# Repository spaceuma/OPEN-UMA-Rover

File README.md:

# UMA Open Source Rover ROS2
Open hardware and software rover developed by Malaga University

*Authors:* C.J. Pérez del Pulgar, Ricardo Sánchez Ibáñez, Patricio López Lupiañez, Francisco de Asís Delgado Rivero, Laura Marta Mantoani and Danil Rivero Pavlenko

*Contact info:* carlosperez@uma.es

*Affiliation:* University of Malaga, [Space Robotics Lab](https://www.uma.es/robotics-and-mechatronics/info/107542/robotica-espacial/)

## Overview
The OpenUmaRov is an open source mobile robotic platform that allows anyone to build it with a maximum cost of 700€, taking into account that the Reach M+ GPS can be replaced with whatever GPS that works with NMEA sentences: just connecting it to the Raspberry Pi through USB port, thanks to the ROS node the GPS can publish NMEA sentences in different topics. This means that, replacing the Reach M+ with a cheaper one, the rover can be built with a maximum cost of 500 €. 

The platform is based on commercial components that can be acquired by Internet. This project involves students and researchers to improve the development of the platform. Moreover, it can be used for teaching and research activities that involves mechanical, engineering, software, electronics and robotics.

## ROS2 

An adaptation of the original code to ROS2 Humble has been developed. This enables the use of the Rover with the Middleware ROS2. 

### Guide

First you need to setup your package and your workspace. Use the package in this repository inside the workspace.

Then make sure to source the package and build the workspace.
```
 source install/setup.bash
 colcon build
```

### Troubleshooting

Issues might appear while setting up your workspace.

- setuptools 58.2 for colcon build sterr output error due to deprecated version.

https://answers.ros.org/question/396439/setuptoolsdeprecationwarning-setuppy-install-is-deprecated-use-build-and-pip-and-other-standards-based-tools/

```
pip install setuptools==58.2.0
```

Install serial
Guide: https://create.arduino.cc/projecthub/ansh2919/serial-communication-between-python-and-arduino-e7cce0

```
pip install pyserial
```

Info. about the Twist format for the msg variable which holds the data received from the topic.

http://docs.ros.org/en/noetic/api/geometry_msgs/html/msg/Twist.html

### Running the node

To run the node once sourced and built.

```
ros2 run rov_node_pkg ROS2UMARov
```

## Rover URDF

In order to test the Rover in a simulated environment, a URDF file of the OpenUMARov has been developed.

## Rover SDF

To implement Rover simulations on Gazebo, it is necessary to develop the SDF Model of it. 

This model uses the following plugins.

- GPS Plugin to simulate such in the simulation environment.
- IMU to simulate the orientation of the Rover.
- Differential drive Model to implement the movement of the Rover 
- Joint State Publisher to know wheels state.

An alternative for NAV2 has been implemented as en extended model.

## Joystick Control

A good way to easily control the Rover is by using the Teleoperation Joystick Control.

By default, it uses the ```ps3_config.yaml``` file.

To test this package a F-710 Game Pad with a USB with Bluetooth connection was used, even though the ```.config``` file is for the PS3 Joystick. If you wish to use a Bluetooh joystick control, you have to edit the directory of the connection to rather the Bluetooth direction, using a USB connection is recommended nonetheless.

To use it with the PC the following changes should be done:

- Add permissions to read/write Serial: 

```
sudo adduser $USER $(stat --format="%G" /dev/ttyACM0)
```

- Build the package with the following command:

```
colcon build --allow-overriding teleop_twist_joy
```

PS3 is default, to run for another config (e.g. xbox) use this:

```
ros2 launch teleop_twist_joy teleop-launch.py
```

Note: this launch file also launches the joy node so do not run it separately.

Only if required:

- Uninstall the default joystick teleop. from ROS2 Lib. Head to opt/ros/lib and remove the file teleop_twist_joy. 
- The last step is due to ROS2 using the config. of the default driver and its parameters instead of your package.
- Launch the driver as normally.

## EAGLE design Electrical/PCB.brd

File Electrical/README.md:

# OPEN-UMA-Rover/Electrical
In this folder there are the files for the PCB board in Eagle, version 7.6.0.

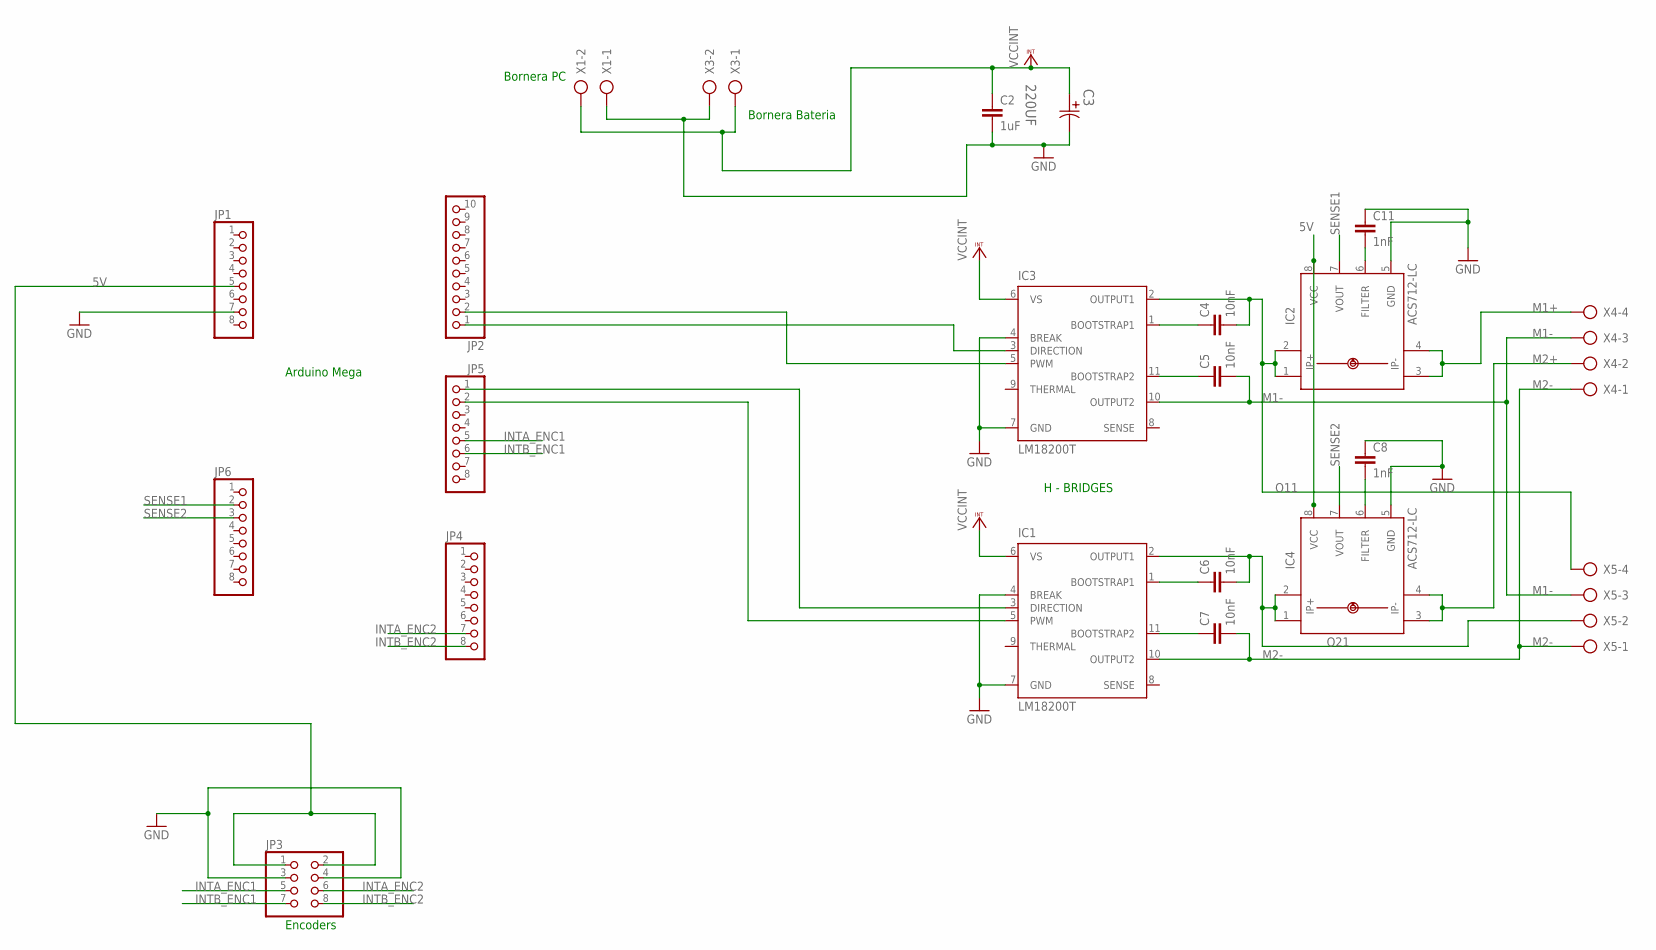
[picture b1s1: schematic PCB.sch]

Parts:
C2: 1uF; C050-030X075
C3: 220UF; CAPPR500-1000X3200
C4, C5, C6, C7: 10nF; C050-030X075
C8, C11: 1nF; C050-030X075
IC1, IC3: LM18200T; TO-220-11
IC2, IC4: ACS712-LC; SOIC8
JP1, JP4, JP5, JP6: PINHD-1X8; 1X08
JP2: PINHD-1X10; 1X10
JP3: PINHD-2X4; 2X04
X1, X3: AK500/2
X4, X5: AK500/4-H

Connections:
5V: IC2.8 (VCC), IC4.8 (VCC), JP1.5, JP3.1, JP3.2
GND: C2.2, C3.2, C8.1, C11.1, IC1.4 (BREAK), IC1.7 (GND), IC2.5 (GND), IC3.4 (BREAK), IC3.7 (GND), IC4.5 (GND), JP1.7, JP3.3, JP3.4, X1.1, X3.2
INTA_ENC1: JP3.5, JP5.5
INTA_ENC2: JP3.6, JP4.7
INTB_ENC1: JP3.7, JP5.6
INTB_ENC2: JP3.8, JP4.8
M1+: IC2.3 (IP-), IC2.4 (IP-1), X4.4
M1-: C5.2, IC3.10 (OUTPUT2), X4.3, X5.3
M2+: IC4.3 (IP-), IC4.4 (IP-1), X4.2
M2-: C7.2, IC1.10 (OUTPUT2), X4.1, X5.1
unnamed: IC3.3 (DIRECTION), JP2.1
unnamed: IC3.5 (PWM), JP2.2
unnamed: IC1.3 (DIRECTION), JP5.1
unnamed: C4.1, IC3.1 (BOOTSTRAP1)
unnamed: IC1.5 (PWM), JP5.2
unnamed: C8.2, IC4.6 (FILTER)
unnamed: C11.2, IC2.6 (FILTER)
unnamed: C5.1, IC3.11 (BOOTSTRAP2)
unnamed: C6.1, IC1.1 (BOOTSTRAP1)
unnamed: C7.1, IC1.11 (BOOTSTRAP2)
O11: C4.2, IC2.1 (IP+), IC2.2 (IP+1), IC3.2 (OUTPUT1), X5.4
O21: C6.2, IC1.2 (OUTPUT1), IC4.1 (IP+), IC4.2 (IP+1), X5.2
SENSE1: IC2.7 (VOUT), JP6.2
SENSE2: IC4.7 (VOUT), JP6.3
VCCINT: C2.1, C3.1, IC1.6 (VS), IC3.6 (VS), X1.2, X3.1

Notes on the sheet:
Encoders
Arduino Mega
H - BRIDGES
Bornera Bateria
Bornera PC

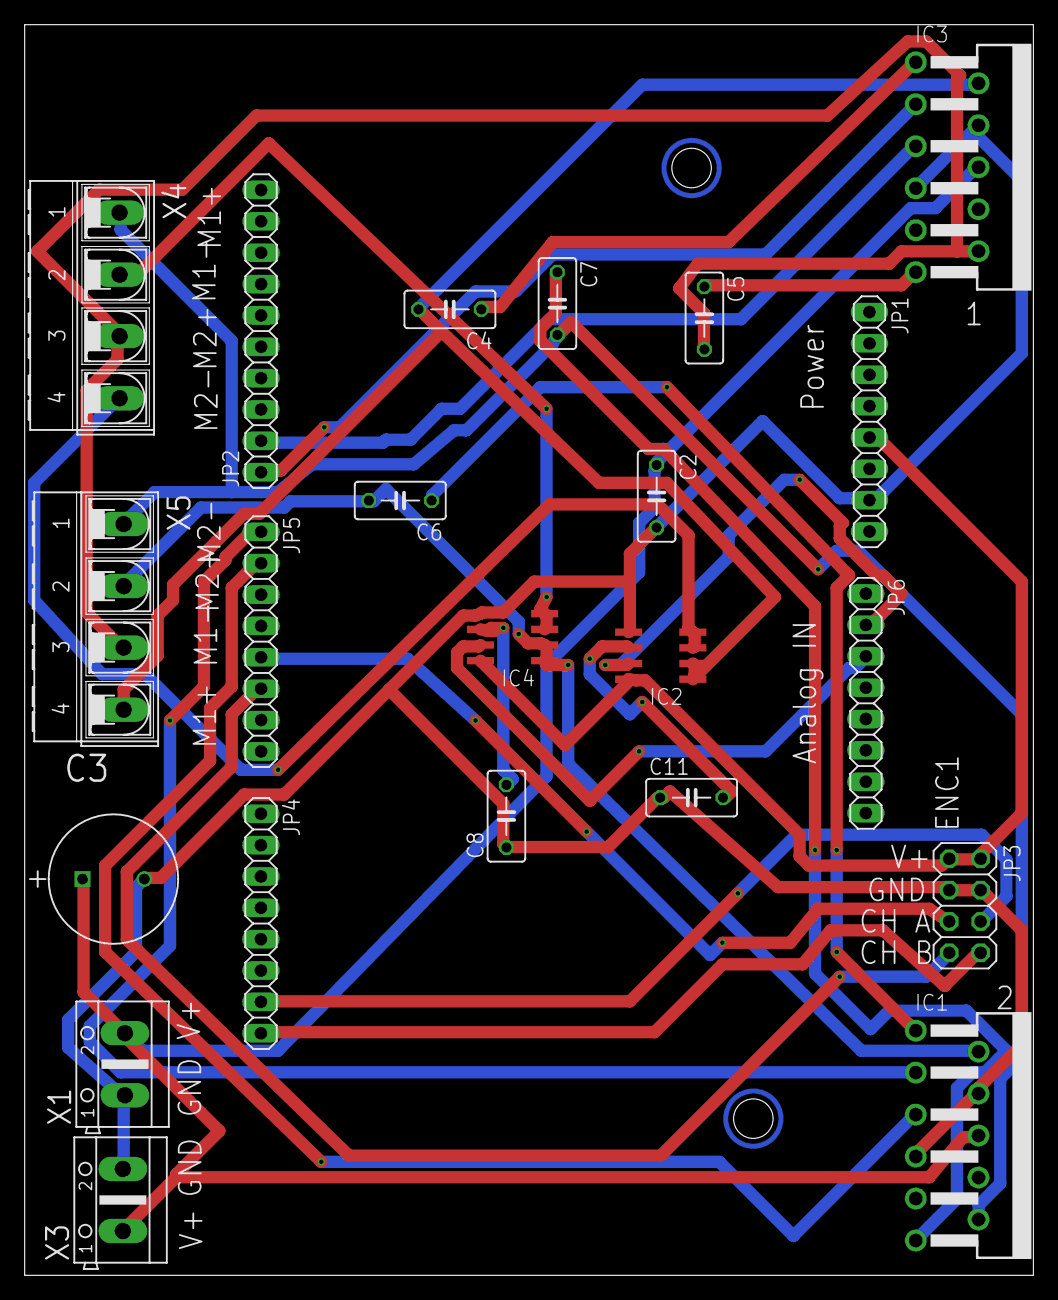
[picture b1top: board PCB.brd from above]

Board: 6 copper layers, 81.7 x 101.3 mm, 22 parts (0 on the bottom side), 25 nets.

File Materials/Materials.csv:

Component;Quantity;Farnell;Link to buy;PRICE ();;;;;;;;;
Chasis + 4 wheels + 4 engines;1;;;247.64;;;;;;;;;
Encoder Lynxmotion;2;;https://www.robotshop.com/es/es/codificador-motor-cuadratura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;69.44;;;;;;;;;
Arduino Mega 2560;1;;;16.95;;;;;;;;;
Fuse holder;1;;;0.5;;;;;;;;;
Fuse 4A;1;;;0.1;;;;;;;;;
Connector 2.5mm;1;;;1.06;;;;;;;;;
Rechargeable battery NiMH 12 Vdc 2800 mAh;1;;;48.99;;;;;;;;;
Capacitor 1uF;1;2112910;;0.28;;;;;;;;;
Capacitor 220uF;1;1219481;;0.75;;;;;;;;;
Capacitor 10nF;4;1141772;;0.76;;;;;;;;;
Capacitor 1nF;2;1902259;;0.78;;;;;;;;;
LM18200T;2;1468979;;31.16;;;;;;;;;
ACS712-LC;2;1329623;;8.18;;;;;;;;;
Pin header 2X04;1;1593441;;0.04;;;;;;;;;
Connector AK500/2;2;2493622;;0.6;;;;;;;;;
Connector AK500/4-H;2;2490940;;3.8;;;;;;;;;
Pin header 1X08;4;;;1.32;;;;;;;;;
Pin header 1X10;1;;;0.4;;;;;;;;;
SparkFun GPS Logger Shield;1;;;49.95;;;;;;;;;
;;;TOTAL;482.7;;;;;;;;;
;;;;;;;;;;;;;
;;;;;;;;;;;;;
;;;;;;;;;;;;;
;;;;;;;;;;;;;
;;;;;;;;;;;;;
;;;;;;;;;;;;;
;;;;;;;;;;;;;
;;;;;;;;;;;;;
;;;;;;;;;;;;;
;;;;;;;;;;;;;
;;;;;;;;;;;;;
;;;;;;;;;;;;;
;;;;;;;;;;;;;
;;;;;;;;;;;;;TOTAL

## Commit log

2019-07-19 Remove images
2019-07-19 Change software folders
2019-07-19 Changes in some folders
2019-07-19 Updating the README files
2019-07-19 Updating list of material
2019-07-19 Changing list of material
2019-07-19 Updating materials
2020-09-22 Remove files and materials modification
2020-09-24 Codes update
    Addition of the LabVIEW GUI, the OpenUMARov Python node and the nmea_navsat_driver node for GPS, and changes of the Arduino code.
2020-09-29 PhotosChanges
2020-10-08 Arduino codes changes
2020-10-08 Update README.md
    Replaced serial by USB.
2022-10-05 Nodo para uso con ROS2 Humble
    Nodo de Python junto con el archivo de Arduino para su uso con ROS2 Humble.
2022-10-05 ROS2 Guide
    Explains how to setup and use the ROS2 node.
2022-10-05 Actualizado con explicación
2022-10-10 Código actualizado y ordenado
    Se han ordenado una serie de variables, actualizado el formato de datos mostrados por terminal y quitado errores.
2022-10-27 Rover URDF
    Se incluye el URDF del Open UMA Rov para posteriores simulaciones
2022-10-27 URDF
2022-10-27 Adición del URDF
2022-10-27 Joystick Control Driver
2022-10-27 Joystick control and rqt_steering control
2022-10-28 Fixed issues with Buffer overlflows
    Now the Rover works flawlessly without any interruption or delays
2022-10-28 General changes and updates
2022-11-16 Small changes to Joystick control package info.
2022-11-18 Gazebo SDF Model Implemented
2022-11-18 SDF Model
2022-11-18 Updated SDF
2022-11-22 Removing materials not necessary in this branch.
2022-11-22 Updated package with SDF Files and URDF
2022-11-22 urdf and sdf models adapted to nav2
    This content must be placed in your "nav2_brigup" directory.
2022-11-24 Filtro digital introducido en el código Arduino
    Se introduce un filtro digital para obtener una respuesta más suave debido a que en cambios bruscos de consigna el controlador no era capaz de alcanzar esta consigna debido al elevado error provocado.
2022-11-24 Updated parameters of the Joystick control
2022-11-25 Updated PI Values and corrected digital filter
2022-11-25 Updated and corrected some issues
2022-11-28 Updated controller and publish encoder info
    Updated the PI in the Arduino code and added a digital filter to smooth the PWM signal sent to the motors in order to avoid an unstable system.
    The ROS2 node now receives information from the Arduino with information about the encoders. This information is later published in newly made topics.
2022-11-28 Removed non updated directory
2022-11-28 Updated values to lower latency
    Updated ROS2 Node to lower the spin frequency and updated to Arduino code to have lower latency by updating the digital filter
2022-12-21 Diseños 3D para Rover
2023-01-11 Added Image
2023-03-31 Engranajes dedicados a la correa de OPENUMA
2023-05-15 Updated folders and files required to run OPENUMA with ROS2
2023-05-16 Update README.md with a simpler and shorter explanation
2023-05-16 Update README.md joystick config.
2023-06-14 Updated the structure of the repository
2023-06-14 Updated README Images
2023-06-14 Path to Teleop Twist
2023-06-14 Add path to rover package
2023-06-14 Added files for IMU
